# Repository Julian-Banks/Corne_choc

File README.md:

# Corne Choc — Wireless Build

A wireless, hot-swappable Corne (crkbd) split keyboard built around Kailh Choc V2 switches and the Corne Chocoflan PCB.

## Final Build Spec

| Decision | Choice |
| --- | --- |
| **Layout** | Corne (3×6 + 3 thumb, split) |
| **PCB** | [Corne Chocoflan](https://github.com/ergomechstore/Corne-chocoflan) (wireless, choc-spaced) |
| **Switches** | Kailh Choc V2 Low Profile — White Rain, Black Cloud, Ghost  |
| **Microcontroller** | SuperMini nRF52840 (cheap Nice!Nano-compatible alternative) |
| **Wireless** | Yes (ZMK / nRF52840) |
| **OLED** | Yes — SSD1306 |
| **Hot-swap** | Yes — Kailh Choc sockets |
| **LEDs** | No (skipped to preserve battery on wireless) |
| **Keycaps** | Choc V2 blanks (surprisingly nice quality) |
| **Case** | [Wireless Corne Chocoflan minimal case](https://www.printables.com/model/1020389-wireless-corne-chocoflan-minimal-keyboard-case/files) |

## Guides & References

- **Official Corne Choc docs** — [foostan/crkbd](https://github.com/foostan/crkbd/tree/main/docs/corne-chocolate)
- **Build log inspiration** (V1 caps, no hot-swap) — [Choc Spaced Corne Wireless](https://github.com/rafaeldelboni/buildlogs/blob/main/crkbd-choc-spaced-switch.md)
- **Chocoflan build blog** — [sascha.sh: I built another mechanical keyboard](https://sascha.sh/posts/i-built-another-mechanical-keyboard/)

### Microcontroller notes
- **SuperMini nRF52840** *(chosen)* — cheap (~$3–5 each), well documented for a Chinese alternative. [Reddit overview](https://www.reddit.com/r/ErgoMechKeyboards/comments/16q5b2c/supermini_nrf52840_a_6_nicenano_20_compatible_mcu/) · [Alternatives wiki](https://github.com/joric/nrfmicro/wiki/Alternatives)
- **Nice!Nano** — the standard, well-documented option, but pricey (~$24 each + shipping).

### Switch references
- [Kailh Choc Switch Impressions](https://www.youtube.com/watch?v=mxUqfPf_1B0)
- [Kailh Choc V2 Red Low-Profile Sound Test](https://www.youtube.com/watch?v=VXPfzeLmQ5g)

### Keycap references (alternatives considered)
- [3D-print: Choc Louder keycaps (choc + MX spacing)](https://www.printables.com/model/1066117-choc-louder-keycaps-choc-and-mx-spacing/files)
- [Resin-printed low-profile caps](https://www.thingiverse.com/thing:4862025)

### Case references (alternatives considered)
- [Slim wireless Corne case](https://www.printables.com/model/416378-wireless-corne-case)
- [Carry case with travel box](https://www.printables.com/model/544127-wireless-corne-choc-v2-case-with-travel-box/files)
- [Case with OLED cover (5×3 Typeractive)](https://www.printables.com/model/441819-wireless-corne-case-5x3-typeractive)

## Bill of Materials

### Electrical Parts

| Part | Specific Part | Link | QTY | Notes |
| --- | --- | --- | --- | --- |
| Microcontroller | SuperMini nRF52840 | | 2 | Cheap alternative to the Nice!Nano |
| MCU headers | | [AliExpress](https://www.aliexpress.com/item/32896689725.html) | 10 × 40-pin (400 pins) | |
| PCB | Corne Chocoflan | [repo](https://github.com/ergomechstore/Corne-chocoflan) | 5 pairs | |
| Switches | Kailh Choc V2 Low Profile — White Rain | [AliExpress](https://www.aliexpress.com/item/1005009022408681.html) | 90 | |
| Switches | Kailh Choc V2 Low Profile — Black Cloud | [AliExpress](https://www.aliexpress.com/item/1005009022408681.html) | 90 | |
| Switches | Kailh Choc V2 Low Profile — Ghost | [AliExpress](https://www.aliexpress.com/item/1005007404357477.html) | 90 | |
| Hot-swap sockets | Kailh Choc sockets | [AliExpress](https://www.aliexpress.com/item/1005008954571807.html) | 220 | |
| Keycaps | Choc V2 blanks | [AliExpress](https://www.aliexpress.com/item/1005009100305250.html) | 220 | Nicer quality than expected |
| Diodes | 1N4148W SMD | [AliExpress](https://www.aliexpress.com/item/32921490945.html) | | |
| OLED display | SSD1306 | [AliExpress](https://www.aliexpress.com/item/1005008640132638.html) | 10 | |
| On/off switch | | [AliExpress](https://www.aliexpress.com/item/1005003829889015.html) | 20 | |
| Reset buttons | Momentary push buttons | [AliExpress](https://www.aliexpress.com/item/1005002201965659.html) | 100 | |
| Battery | LiPo 3.7V 120mAh (PH2.0 connector) | [DIY Electronics](https://www.diyelectronics.co.za/store/li-ion-li-po/6707-lipo-battery-37v-120mah-25x24x35mm-1c-1cell-with-ph20-connector.html) | 2 | |

### Mechanical Parts

Driven by the Chocoflan PCB and the minimal case choice.

| Part | Specific Part | Link | QTY | Notes |
| --- | --- | --- | --- | --- |
| Case | Wireless Corne Chocoflan minimal case | [Printables](https://www.printables.com/model/1020389-wireless-corne-chocoflan-minimal-keyboard-case/files) | 1 set | 3D printed |
| Bottom Plate  | See `plate_cut*.dxf` / `.svg` in repo  | | | lazer cut from Aluminimum |
| Switch plate | See `plate_cut*.dxf` / `.svg` in repo  | | | lazer cut from Aluminimum |
| Standoffs + screws | | | | |
| PK-662 tenting stands | | | | |

## Firmware Setup & Configuration

This board runs [ZMK](https://zmk.dev). Firmware is built in the cloud by GitHub Actions — no local toolchain needed. Full guide: [zmk.dev/docs/user-setup](https://zmk.dev/docs/user-setup).

**Setup (once):**
1. Run the ZMK setup script (or `zmk init`) to create your config repo.
2. Choose the keyboard and controller when prompted:
   - **Keyboard / shield:** `Corne`
   - **Board:** `nice_nano_v2` (the SuperMini nRF52840 is nice!nano-compatible)
3. Push the repo to GitHub.

**Configure:**
- Keymap lives in `config/corne.keymap` — edit layers, combos, behaviors here.
- Feature flags live in `config/corne.conf` — e.g. enable the OLED and disable RGB:
  ```ini
  CONFIG_ZMK_DISPLAY=y
  # no underglow / per-key LEDs on this build
  ```

**Build & flash:**
1. `git push` → GitHub Actions builds automatically.
2. Download the `firmware` artifact from the Actions tab — it contains the `.uf2` files (one per half, plus a `settings_reset`).
3. Double-tap reset on a half to enter bootloader, then drag the matching `.uf2` onto the USB drive that appears. Repeat for the other half.

## Credits

- **PCB** — [Corne Chocoflan by ergomechstore](https://github.com/ergomechstore/Corne-chocoflan). The Gerbers and KiCad source in `PCB/` are vendored from this open-source project.
- **Layout** — [Corne (crkbd) by foostan](https://github.com/foostan/crkbd).
- **Case** — [Wireless Corne Chocoflan minimal case](https://www.printables.com/model/1020389-wireless-corne-chocoflan-minimal-keyboard-case/files).

## Repo Contents

- `PCB/` — pointer to the external Corne Chocoflan PCB design (no source vendored).
- `Laser Cutting/` — switch/plate cut files (`.dxf`, `.svg`, `.pdf`).
- `3D Prints/` — case and cover models (`.step`, `.stl`, `.f3d`), including a custom MK2 chassis and carry case explored during design.
- `images/` — build photos.
- `brainstorming.md` — original decision notes and research (kept for history).

## Build Photos

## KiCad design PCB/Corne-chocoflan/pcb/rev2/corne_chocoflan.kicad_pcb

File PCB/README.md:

# PCB

This build uses the **Corne Chocoflan** (rev2) wireless, choc-spaced PCB — the board that was actually fabricated for this keyboard. The design files are vendored here from the upstream open-source repo.

**Credit:** PCB design by [ergomechstore — Corne-chocoflan](https://github.com/ergomechstore/Corne-chocoflan). All design files in this folder originate from that project.

## What's here — `Corne-chocoflan/`

- `gerber/rev2/corne_chocoflan_gerbers.zip` — **production Gerbers** (upload this to JLCPCB / your fab).
- `gerber/rev2/corne_chocoflan_gerbers/` — the unzipped Gerber + drill files.
- `gerber/rev2/bom_pos/` — BOM and pick-and-place (POS) CSVs for assembly.
- `gerber/rev2/ibom.html` — interactive BOM (open in a browser for placement reference).
- `gerber/rev2/corne_chocoflan.step` — 3D model of the board.
- `pcb/rev2/` — KiCad source (`.kicad_pcb`, `.kicad_sch`, `.kicad_pro`) if you need to edit the design.

KiCad auto-save backups and `.git` history from the upstream clone were dropped to keep the repo lean.

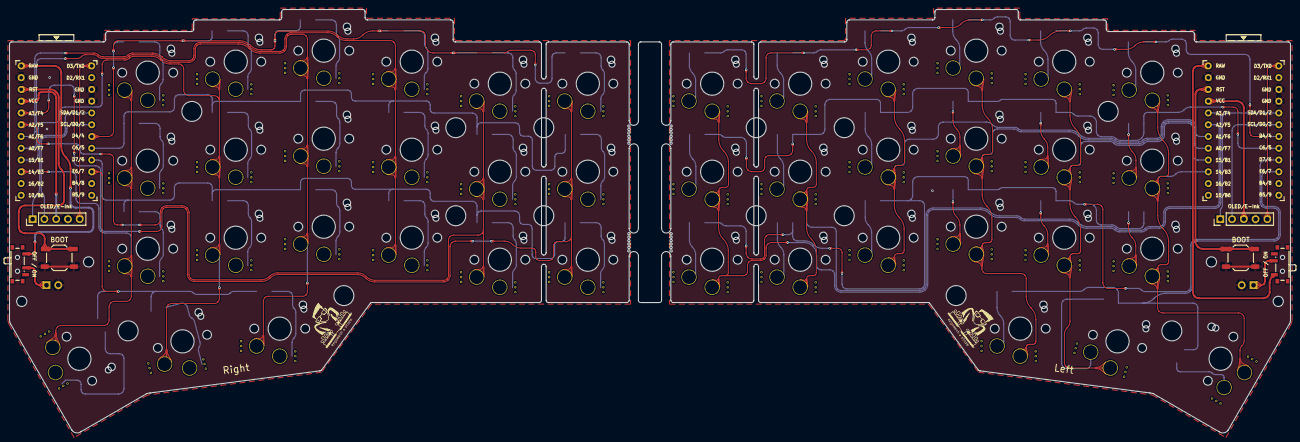
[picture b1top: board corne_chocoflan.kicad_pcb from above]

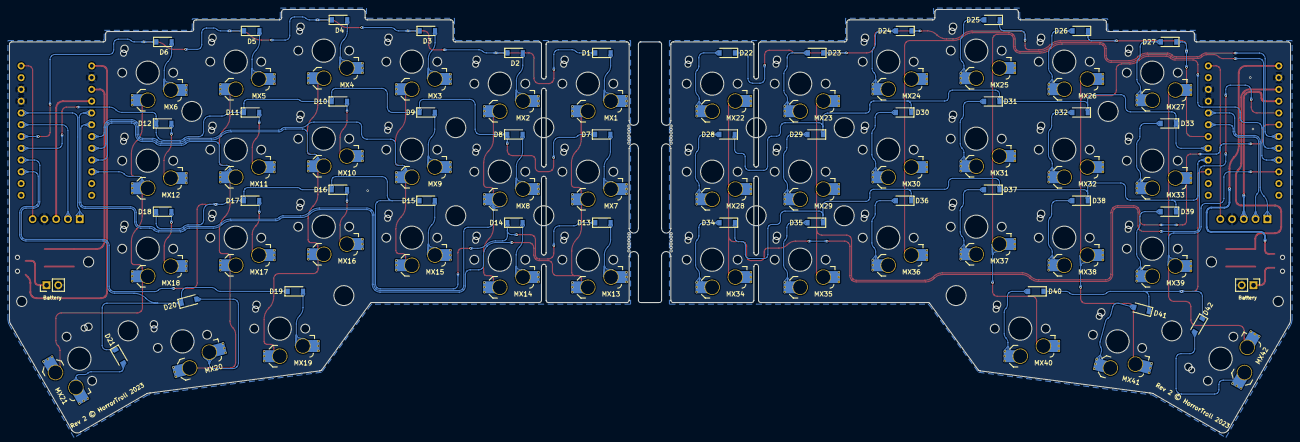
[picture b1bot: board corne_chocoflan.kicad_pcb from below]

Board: 2 copper layers, 276.5 x 91.4 mm, 116 parts (86 on the bottom side), 78 nets.

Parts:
D1, D2, D3, D4, D5, D6, D7, D8, D9, D10, D11, D12, D13, D14, D15, D16, D17, D18, D19, D20, D21: 1N4148W_L; D_SOD-123
D22, D23, D24, D25, D26, D27, D28, D29, D30, D31, D32, D33, D34, D35, D36, D37, D38, D39, D40, D41, D42: 1N4148W_R; D_SOD-123
J1: OLED/E-Ink_L; PinHeader_1x05_P2.54mm_Vertical
J2: Battery_L; PinHeader_1x02_P2.54mm_Vertical
J3: Battery_R; PinHeader_1x02_P2.54mm_Vertical
J4: OLED/E-Ink_R; PinHeader_1x05_P2.54mm_Vertical
M1, M2, M3, M4: Mouse_Bite; mousebites_2mm_big_width
MX1, MX2, MX3, MX4, MX5, MX6, MX7, MX8, MX9, MX10, MX11, MX12, MX13, MX14, MX15, MX16, MX17, MX18, MX19, MX20: 1u_L; SW_choc_v1_v2_HS_1u_corne
MX21: 1.5u_L; SW_choc_v1_v2_HS_1.5u_corne
MX22, MX23, MX24, MX25, MX26, MX27, MX28, MX29, MX30, MX31, MX32, MX33, MX34, MX35, MX36, MX37, MX38, MX39, MX40, MX41: 1u_R; SW_choc_v1_v2_HS_1u_corne
MX42: 1.5u_R; SW_choc_v1_v2_HS_1.5u_corne
SW1: DIP_L; SW_SPDT_PCM12
SW2: BOOT_Pin_L; SW_SPST_TL3342
SW3: DIP_R; SW_SPDT_PCM12
SW4: BOOT_Pin_R; SW_SPST_TL3342
TH1, TH2, TH3, TH4, TH5, TH6, TH7: Screw_M2_TH_L; M2_HOLE_v2
TH8, TH9: Screw_M2_PCB_L; M2_HOLE_v2_corne_2.2mm
TH10, TH11, TH12, TH13, TH14, TH15, TH16: Screw_M2_TH_R; M2_HOLE_v2
TH17, TH18: Screw_M2_PCB_R; M2_HOLE_v2_corne_2.2mm
U1: ProMicro_L; ProMicro_v3
U2: ProMicro_R; ProMicro_v3

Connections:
+3V3: J4.3, U2.21 (VCC)
BOOT_L: SW2.2, U1.22 (RST)
BOOT_R: SW4.2, U2.22 (RST)
CS_L: J1.5, U1.1 (TX0/D3)
CS_R: J4.5, U2.1 (TX0/D3)
Col0_L: MX1.2, MX7.2, MX13.2, U1.20 (F4/A3)
Col0_R: MX22.1, MX28.1, MX34.1, U2.20 (F4/A3)
Col1_L: MX2.2, MX8.2, MX14.2, U1.19 (F5/A2)
Col1_R: MX23.1, MX29.1, MX35.1, U2.19 (F5/A2)
Col2_L: MX3.2, MX9.2, MX15.2, U1.18 (F6/A1)
Col2_R: MX24.1, MX30.1, MX36.1, U2.18 (F6/A1)
Col3_L: MX4.2, MX10.2, MX16.2, MX19.2, U1.17 (F7/A0)
Col3_R: MX25.1, MX31.1, MX37.1, MX40.1, U2.17 (F7/A0)
Col4_L: MX5.2, MX11.2, MX17.2, MX20.2, U1.16 (B1/15)
Col4_R: MX26.1, MX32.1, MX38.1, MX41.1, U2.16 (B1/15)
Col5_L: MX6.2, MX12.2, MX18.2, MX21.2, U1.15 (B3/14)
Col5_R: MX27.1, MX33.1, MX39.1, MX42.1, U2.15 (B3/14)
GND: J1.4, J2.2, SW2.1, U1.3 (GND), U1.4 (GND), U1.23 (GND)
GNDA: J3.2, J4.4, SW4.1, U2.3 (GND), U2.4 (GND), U2.23 (GND)
unnamed: D1.2 (A), MX1.1
unnamed: D2.2 (A), MX2.1
unnamed: D3.2 (A), MX3.1
unnamed: D4.2 (A), MX4.1
unnamed: D5.2 (A), MX5.1
unnamed: D6.2 (A), MX6.1
unnamed: D7.2 (A), MX7.1
unnamed: D8.2 (A), MX8.1
unnamed: D9.2 (A), MX9.1
unnamed: D10.2 (A), MX10.1
unnamed: D11.2 (A), MX11.1
unnamed: D12.2 (A), MX12.1
unnamed: D13.2 (A), MX13.1
unnamed: D14.2 (A), MX14.1
unnamed: D15.2 (A), MX15.1
unnamed: D16.2 (A), MX16.1
unnamed: D17.2 (A), MX17.1
unnamed: D18.2 (A), MX18.1
unnamed: D19.2 (A), MX19.1
unnamed: D20.2 (A), MX20.1
unnamed: D21.2 (A), MX21.1
unnamed: D22.2 (A), MX22.2
unnamed: D23.2 (A), MX23.2
unnamed: D24.2 (A), MX24.2
unnamed: D25.2 (A), MX25.2
unnamed: D26.2 (A), MX26.2
unnamed: D27.2 (A), MX27.2
unnamed: D28.2 (A), MX28.2
unnamed: D29.2 (A), MX29.2
unnamed: D30.2 (A), MX30.2
unnamed: D31.2 (A), MX31.2
unnamed: D32.2 (A), MX32.2
unnamed: D33.2 (A), MX33.2
unnamed: D34.2 (A), MX34.2
unnamed: D35.2 (A), MX35.2
unnamed: D36.2 (A), MX36.2
unnamed: D37.2 (A), MX37.2
unnamed: D38.2 (A), MX38.2
unnamed: D39.2 (A), MX39.2
unnamed: D40.2 (A), MX40.2
unnamed: D41.2 (A), MX41.2
unnamed: D42.2 (A), MX42.2
unnamed: J2.1, SW1.2 (B)
unnamed: J3.1, SW3.2 (B)
Row0_L: D1.1 (K), D2.1 (K), D3.1 (K), D4.1 (K), D5.1 (K), D6.1 (K), U1.7 (4/D4)
Row0_R: D22.1 (K), D23.1 (K), D24.1 (K), D25.1 (K), D26.1 (K), D27.1 (K), U2.7 (4/D4)
Row1_L: D7.1 (K), D8.1 (K), D9.1 (K), D10.1 (K), D11.1 (K), D12.1 (K), U1.8 (5/C6)
Row1_R: D28.1 (K), D29.1 (K), D30.1 (K), D31.1 (K), D32.1 (K), D33.1 (K), U2.8 (5/C6)
Row2_L: D13.1 (K), D14.1 (K), D15.1 (K), D16.1 (K), D17.1 (K), D18.1 (K), U1.9 (6/D7)
Row2_R: D34.1 (K), D35.1 (K), D36.1 (K), D37.1 (K), D38.1 (K), D39.1 (K), U2.9 (6/D7)
Row3_L: D19.1 (K), D20.1 (K), D21.1 (K), U1.10 (7/E6)
Row3_R: D40.1 (K), D41.1 (K), D42.1 (K), U2.10 (7/E6)
SCL_L: J1.2, U1.6 (3/D0/SCL)
SCL_R: J4.2, U2.6 (3/D0/SCL)
SDA_L: J1.1, U1.5 (2/D1/SDA)
SDA_R: J4.1, U2.5 (2/D1/SDA)
VBAT: SW1.1 (A), U1.24 (RAW)
VBATA: SW3.1 (A), U2.24 (RAW)
VCC: J1.3, U1.21 (VCC)

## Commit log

2025-06-19 Brainstorming
2025-06-19 Fixing formating
2026-03-01 some case and cover resources
2026-06-03 chore: bit old re-organise

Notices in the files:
PCB/Corne-chocoflan/pcb/rev2/corne_chocoflan.kicad_pcb:
Copyright © 2023 HorrorTroll
GPL2 License
Rev 2 © HorrorTroll 2023
